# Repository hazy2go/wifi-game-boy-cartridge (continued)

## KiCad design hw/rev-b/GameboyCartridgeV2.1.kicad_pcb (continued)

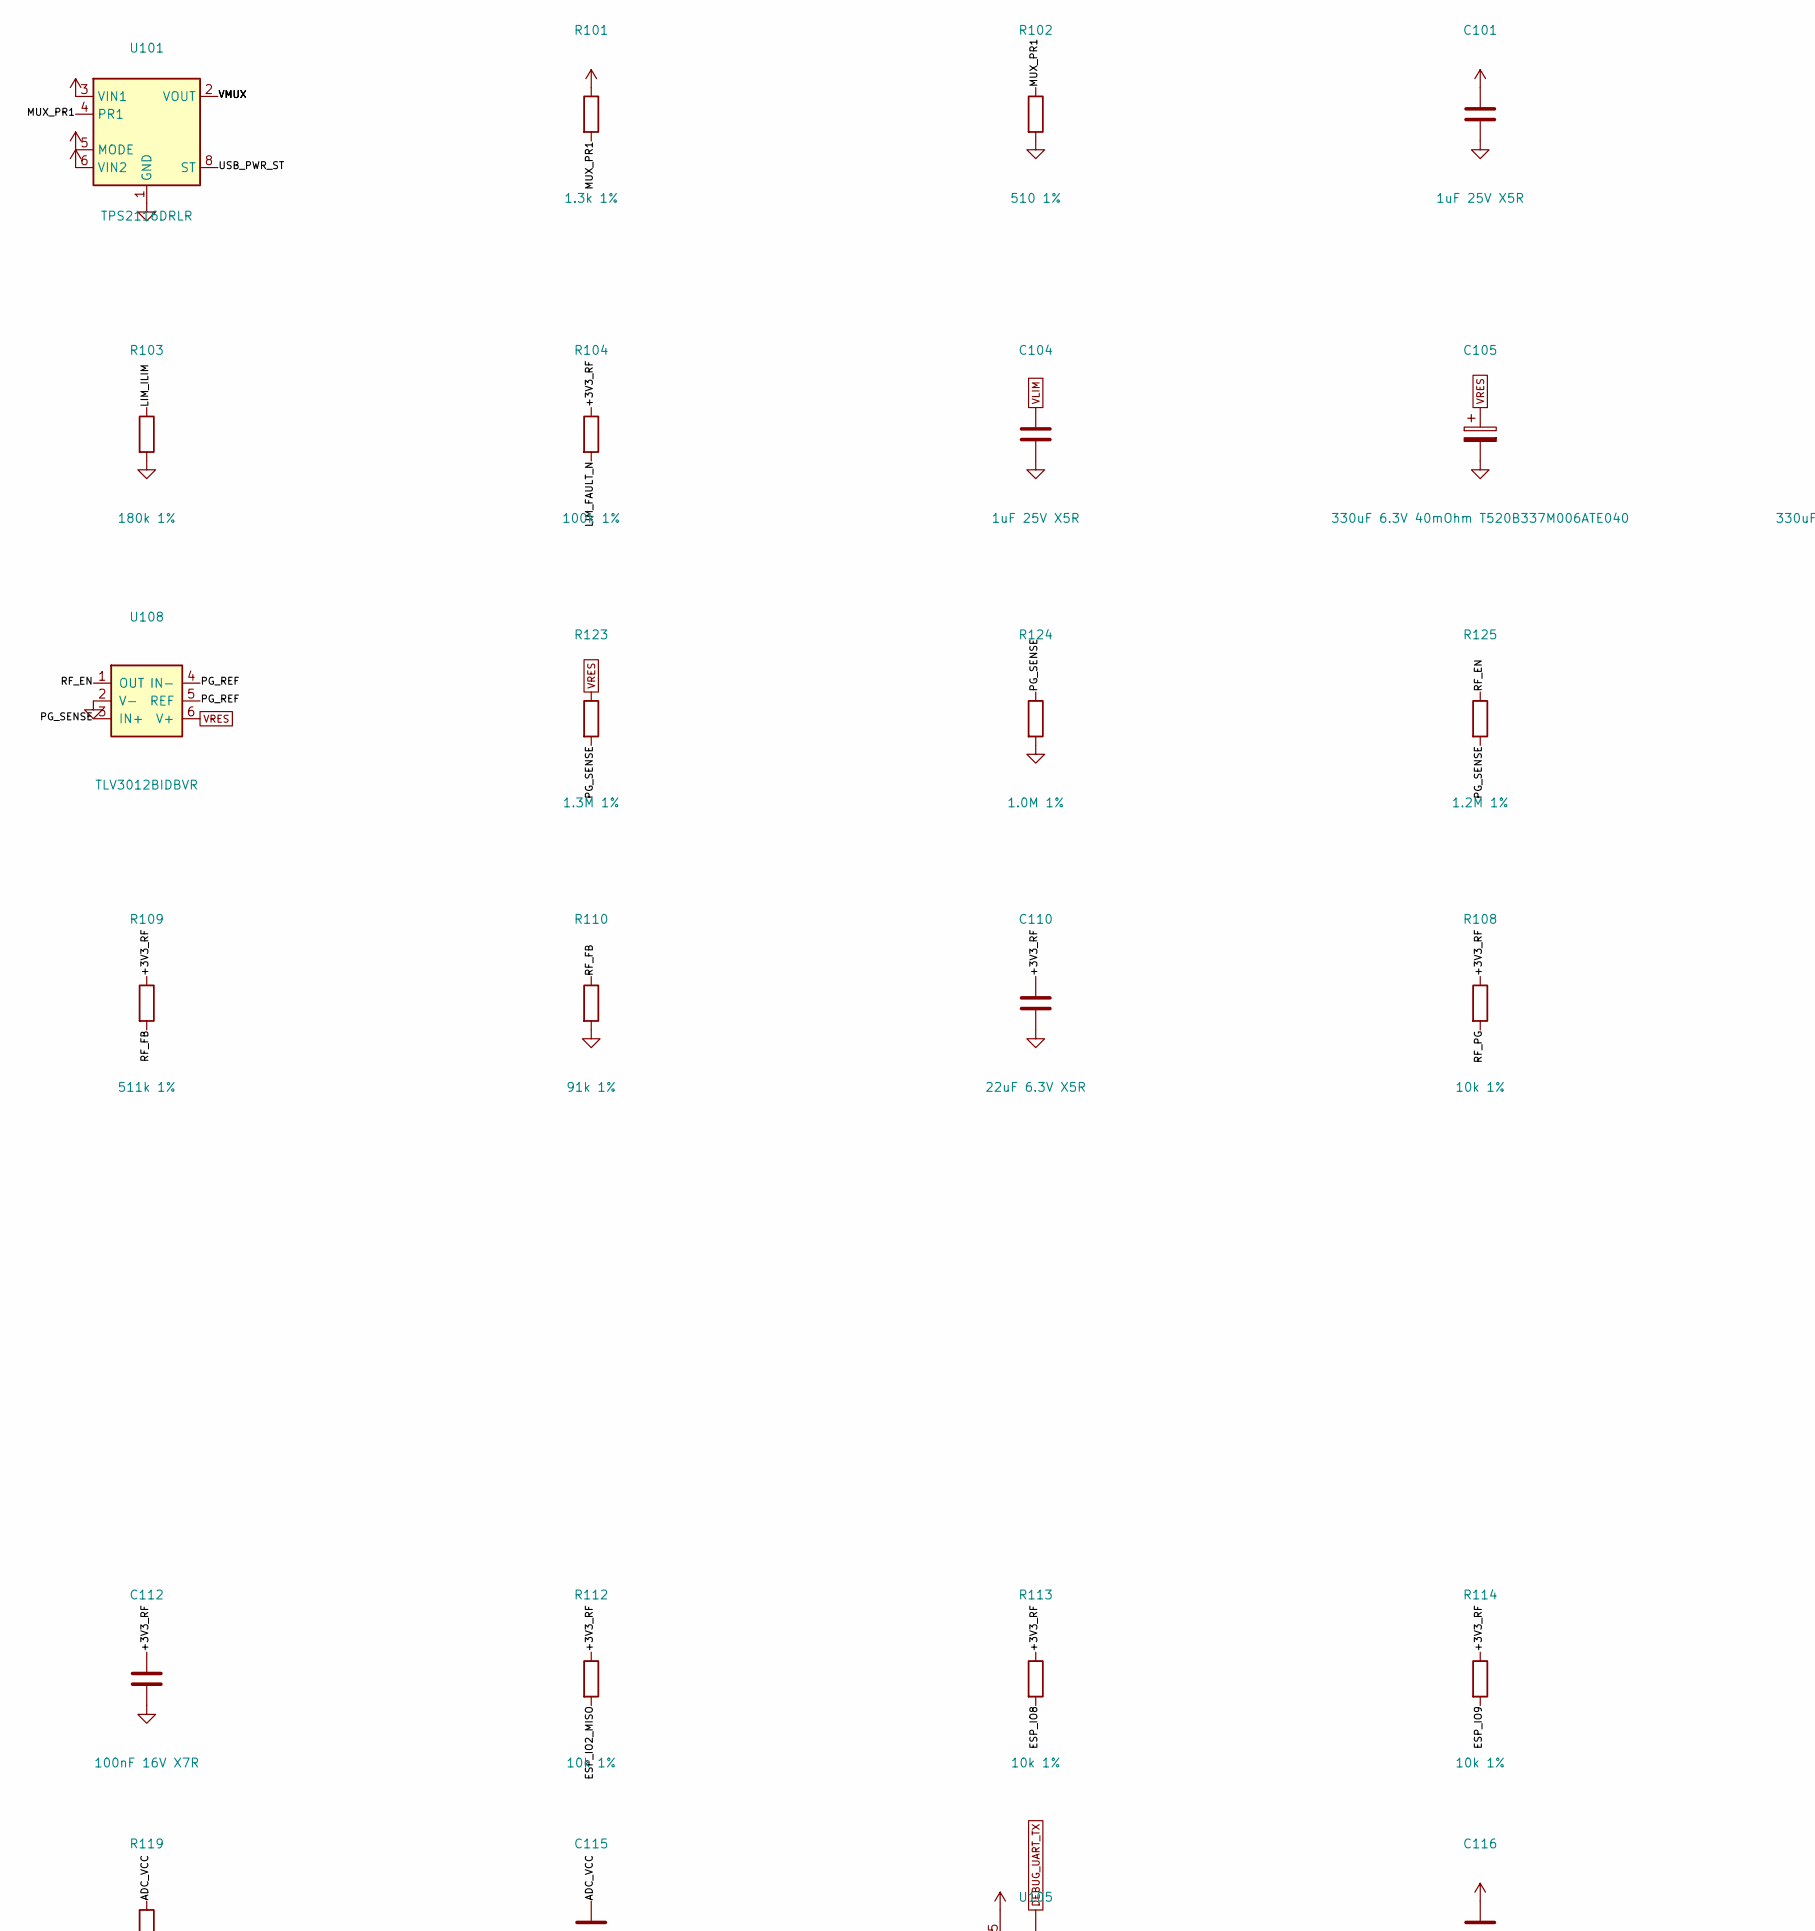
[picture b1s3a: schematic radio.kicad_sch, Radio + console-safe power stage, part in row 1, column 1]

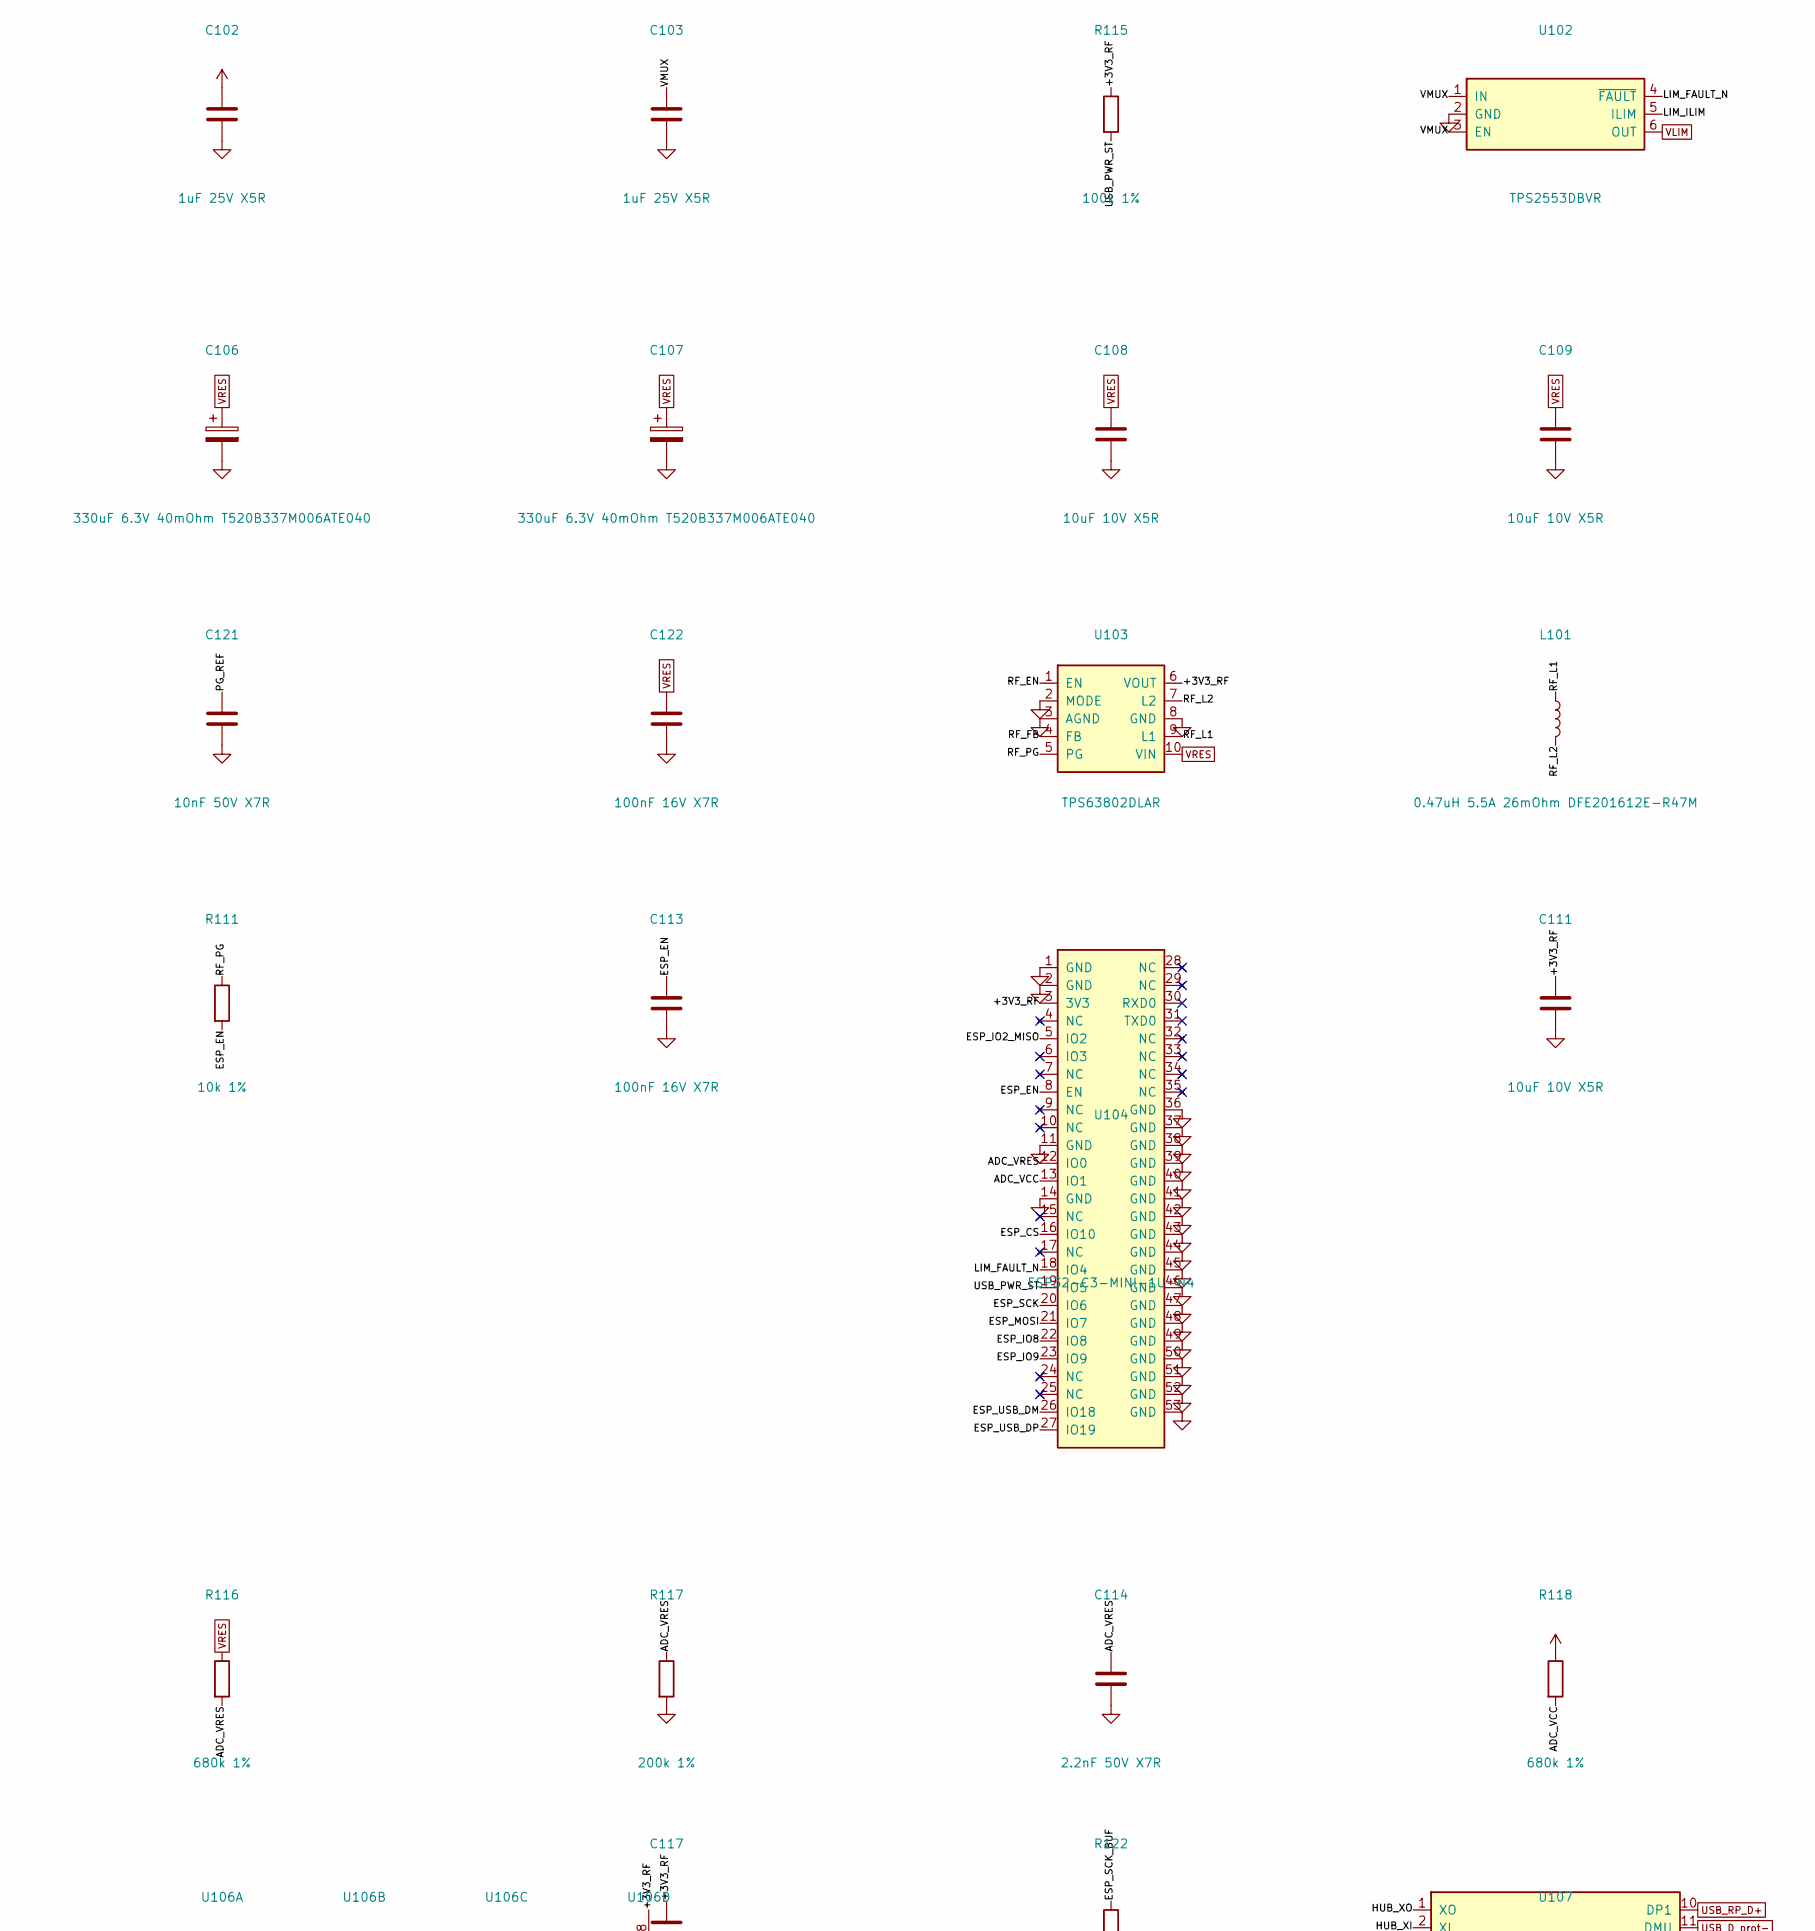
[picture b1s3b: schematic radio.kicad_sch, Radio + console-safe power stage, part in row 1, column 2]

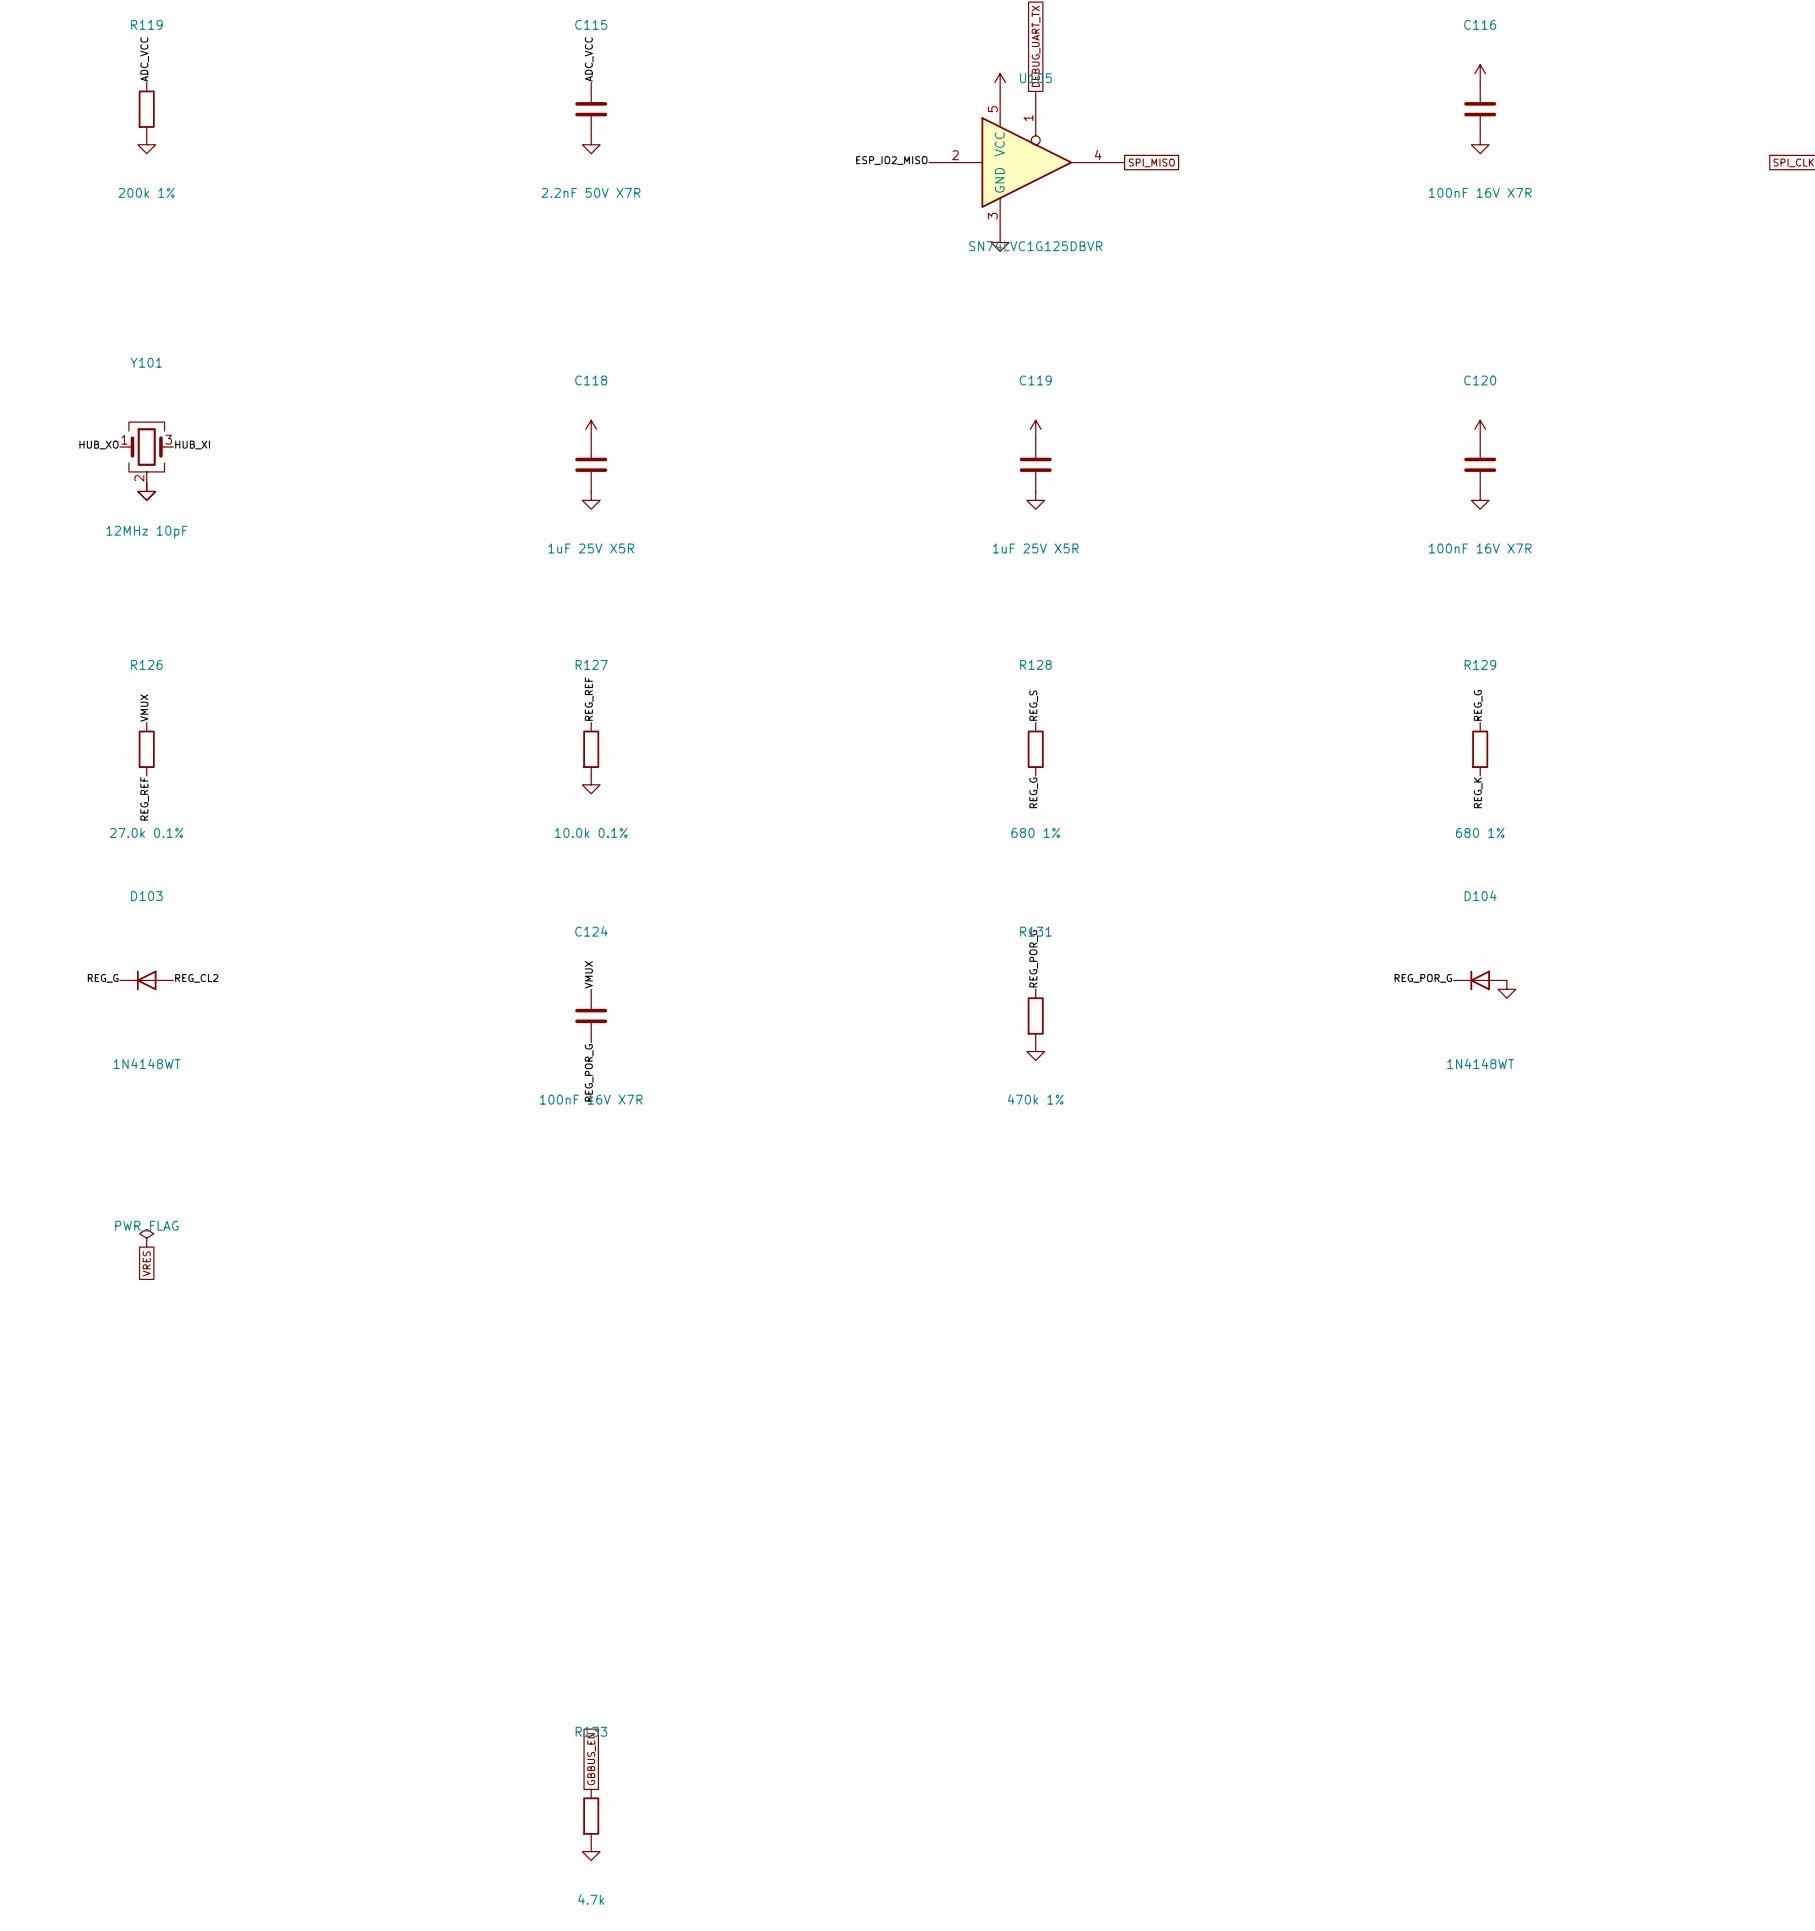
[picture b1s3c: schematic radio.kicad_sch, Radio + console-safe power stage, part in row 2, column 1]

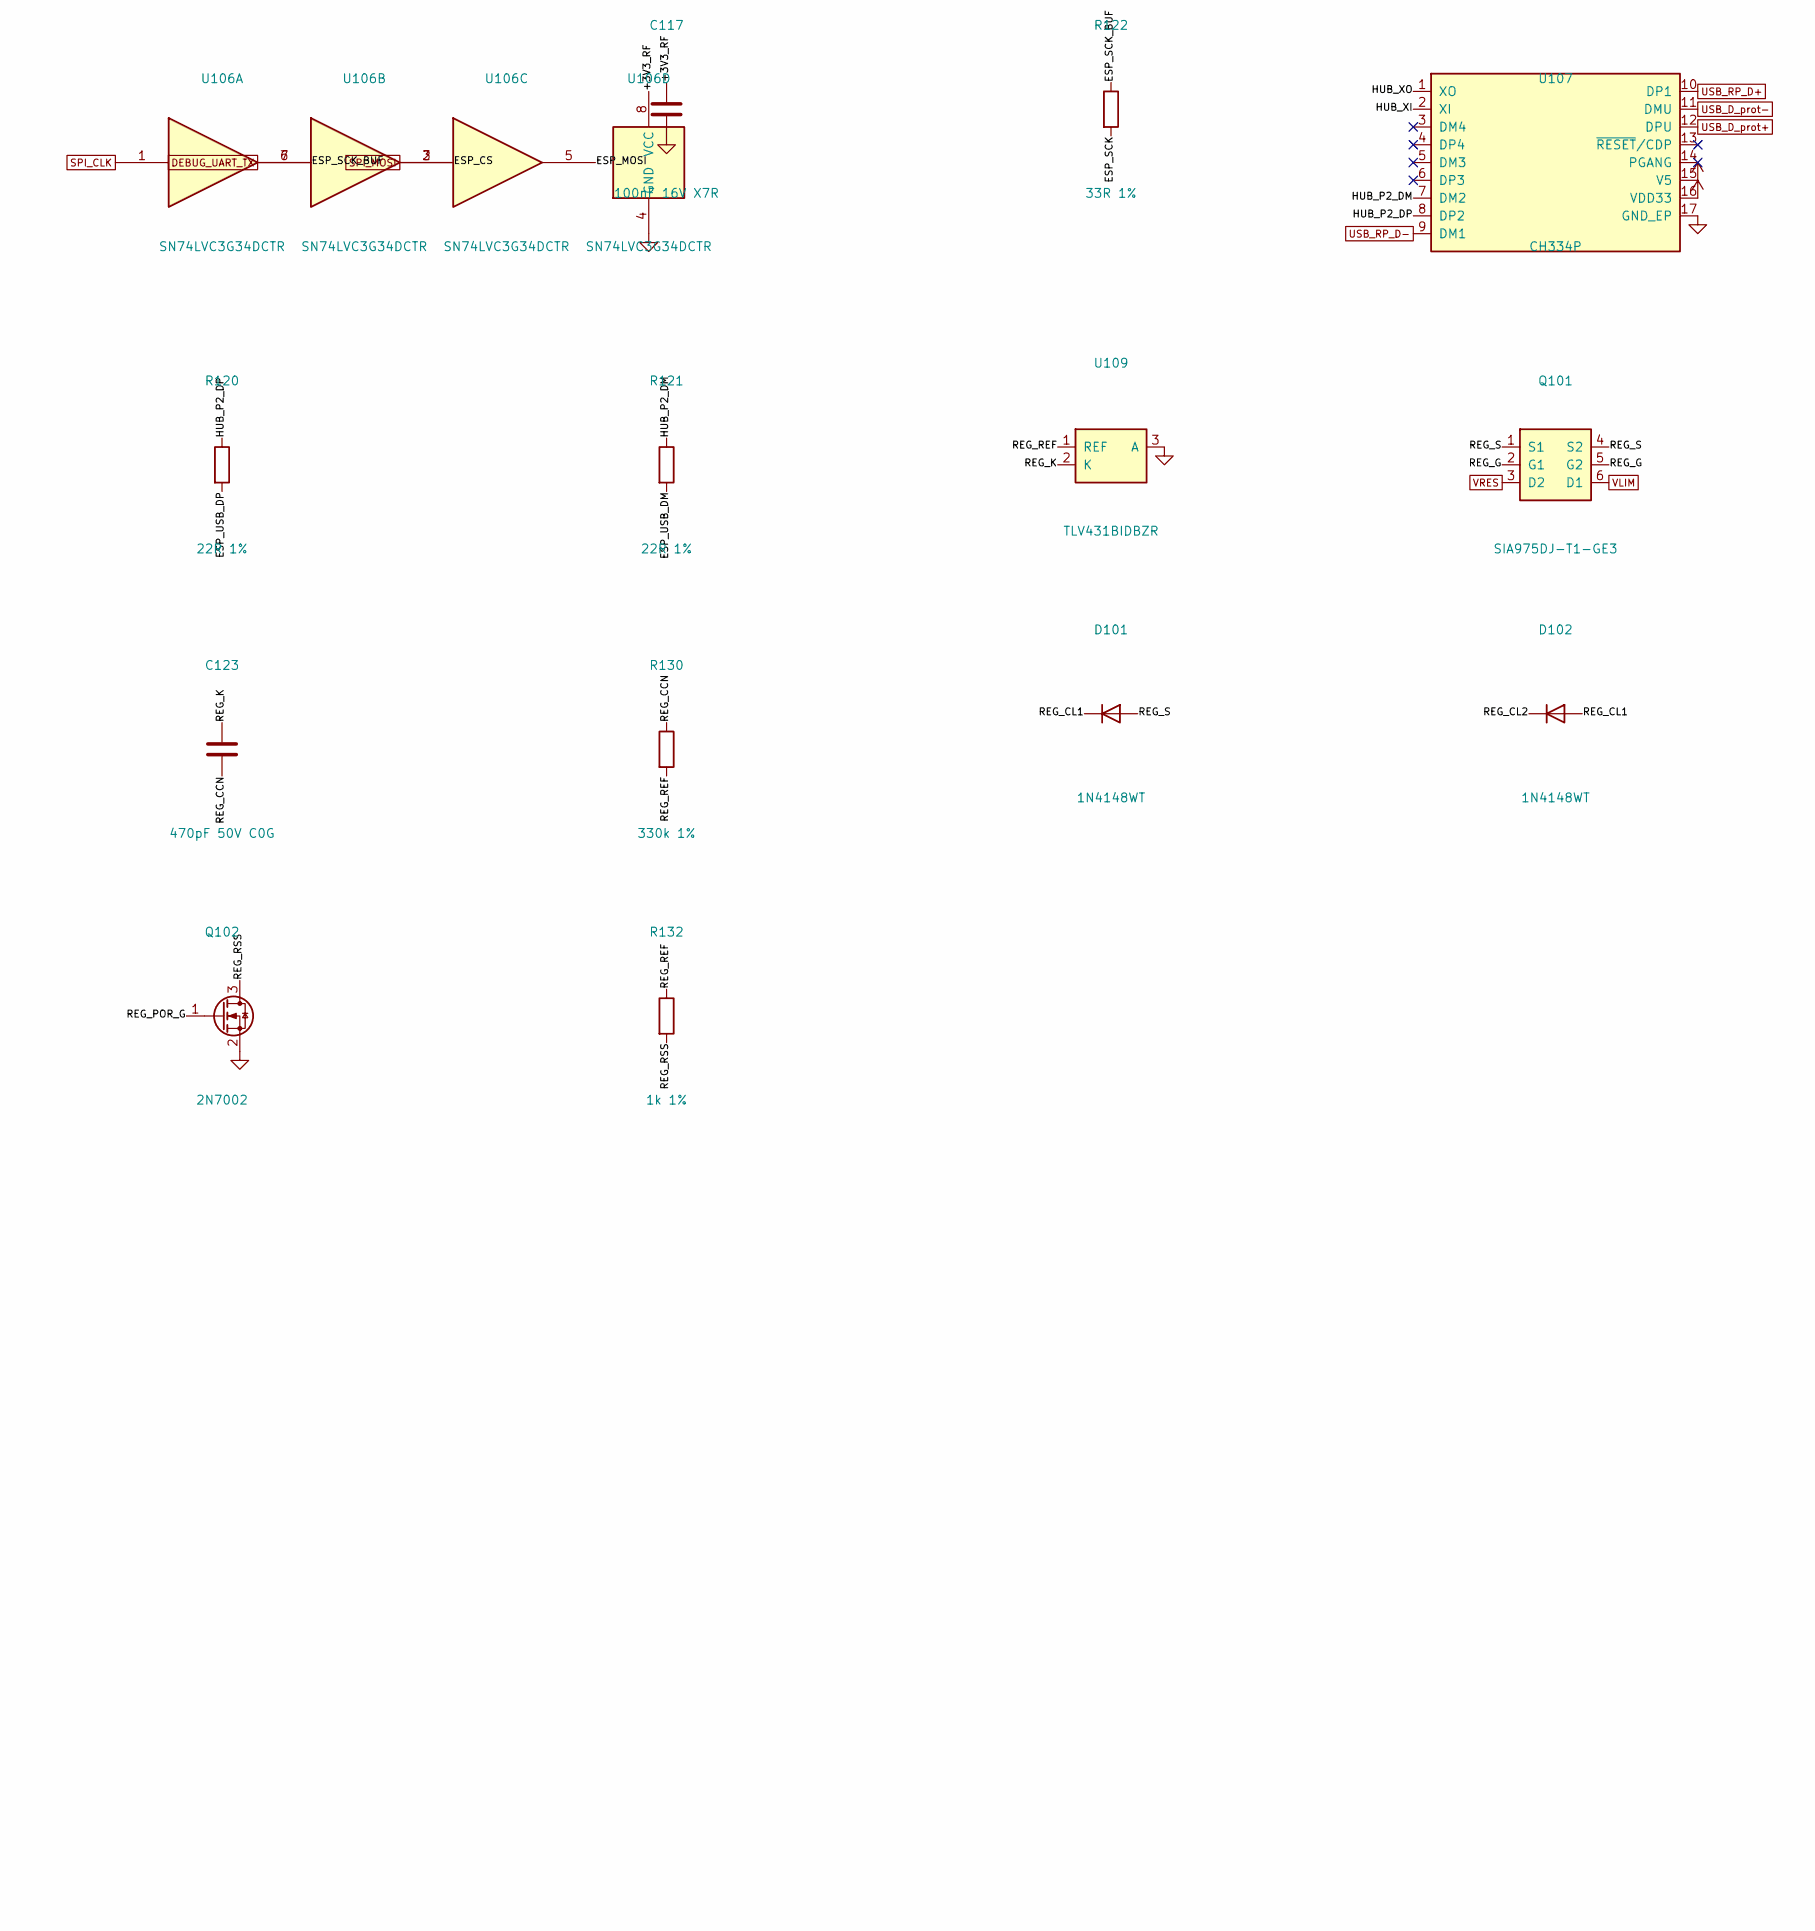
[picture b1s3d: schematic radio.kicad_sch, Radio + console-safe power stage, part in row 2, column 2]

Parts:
C101, C102, C103, C104, C118, C119: 1uF 25V X5R; C_0402_1005Metric; LCSC C52923
C105, C106, C107: 330uF 6.3V 40mOhm T520B337M006ATE040; CP_EIA-3528-21_Kemet-B; LCSC C696806
C108, C109, C111: 10uF 10V X5R; C_0603_1608Metric; LCSC C19702
C110: 22uF 6.3V X5R; C_0603_1608Metric; LCSC C59461
C112, C113, C116, C117, C120, C122, C124: 100nF 16V X7R; C_0402_1005Metric; LCSC C1525
C114, C115: 2.2nF 50V X7R; C_0402_1005Metric; LCSC C84703
C121: 10nF 50V X7R; C_0402_1005Metric; LCSC C15195
C123: 470pF 50V C0G; C_0402_1005Metric; LCSC C76971
D101, D102, D103, D104: 1N4148WT; D_SOD-523; LCSC C27748
L101: 0.47uH 5.5A 26mOhm DFE201612E-R47M; L_Murata_DFE201610P; LCSC C668312
Q101: SIA975DJ-T1-GE3; Vishay_PowerPAK_SC70-6L_Dual; LCSC C141597
Q102: 2N7002; SOT-23; LCSC C8545
R101: 1.3k 1%; R_0402_1005Metric; LCSC C25866
R102: 510 1%; R_0402_1005Metric; LCSC C25123
R103: 180k 1%; R_0402_1005Metric; LCSC C25760
R104, R115: 100k 1%; R_0402_1005Metric; LCSC C25741
R108, R111, R112, R113, R114: 10k 1%; R_0402_1005Metric; LCSC C25744
R109: 511k 1%; R_0402_1005Metric; LCSC C64042
R110: 91k 1%; R_0402_1005Metric; LCSC C453777
R116, R118: 680k 1%; R_0402_1005Metric; LCSC C4131
R117, R119: 200k 1%; R_0402_1005Metric; LCSC C25764
R120, R121: 22R 1%; R_0402_1005Metric; LCSC C25092
R122: 33R 1%; R_0402_1005Metric; LCSC C25105
R123: 1.3M 1%; R_0402_1005Metric; LCSC C423245
R124: 1.0M 1%; R_0402_1005Metric; LCSC C26083
R125: 1.2M 1%; R_0402_1005Metric; LCSC C43675
R126: 27.0k 0.1%; R_0402_1005Metric; LCSC C723421
R127: 10.0k 0.1%; R_0402_1005Metric; LCSC C190095
R128, R129: 680 1%; R_0402_1005Metric; LCSC C137948
R130: 330k 1%; R_0402_1005Metric; LCSC C25778
R131: 470k 1%; R_0402_1005Metric; LCSC C25790
R132: 1k 1%; R_0402_1005Metric; LCSC C11702
R133: 4.7k; R_0402_1005Metric; LCSC C25900
U101: TPS2116DRLR; SOT-583-8; LCSC C3235557
U102: TPS2553DBVR; SOT-23-6; LCSC C55266
U103: TPS63802DLAR; TI_DLA0010A_VSON-HR-10_2x3mm_P0.5mm; LCSC C2845237
U104: ESP32-C3-MINI-1U-N4; ESP32-C3-MINI-1U; LCSC C2911374
U105: SN74LVC1G125DBVR; SOT-23-5; LCSC C23654
U106: SN74LVC3G34DCTR; SSOP-8_2.95x2.8mm_P0.65mm; LCSC C139356
U107: CH334P; QFN-16-1EP_3x3mm_P0.5mm_EP1.75x1.75mm; LCSC C5373042
U108: TLV3012BIDBVR; SOT-23-6; LCSC C20345924
U109: TLV431BIDBZR; SOT-23; LCSC C398375
Y101: 12MHz 10pF; Crystal_SMD_3225-4Pin_3.2x2.5mm; LCSC C20625731

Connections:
+3V3: C116.1, C118.1, C119.1, C120.1, U105.5 (VCC), U107.15 (V5), U107.16 (VDD33); also elsewhere on the board
/Radio/+3V3_RF: C110.1, C111.1, C112.1, C117.1, R104.1, R108.1, R109.1, R112.1, R113.1, R114.1, R115.1, U103.6 (VOUT), U104.3 (3V3), U106.8 (VCC)
/Radio/ADC_VCC: C115.1, R118.2, R119.1, U104.13 (IO1)
/Radio/ADC_VRES: C114.1, R116.2, R117.1, U104.12 (IO0)
/Radio/ESP_CS: U104.16 (IO10), U106.2
/Radio/ESP_EN: C113.1, R111.2, U104.8 (EN)
/Radio/ESP_IO2_MISO: R112.2, U104.5 (IO2), U105.2
/Radio/ESP_IO8: R113.2, U104.22 (IO8)
/Radio/ESP_IO9: R114.2, U104.23 (IO9)
/Radio/ESP_MOSI: U104.21 (IO7), U106.5
/Radio/ESP_SCK: R122.2, U104.20 (IO6)
/Radio/ESP_SCK_BUF: R122.1, U106.7
/Radio/ESP_USB_DM: R121.2, U104.26 (IO18)
/Radio/ESP_USB_DP: R120.2, U104.27 (IO19)
/Radio/HUB_P2_DM: R121.1, U107.7 (DM2)
/Radio/HUB_P2_DP: R120.1, U107.8 (DP2)
/Radio/HUB_XI: U107.2 (XI), Y101.3
/Radio/HUB_XO: U107.1 (XO), Y101.1
/Radio/LIM_FAULT_N: R104.2, U102.4 (~FAULT), U104.18 (IO4)
/Radio/LIM_ILIM: R103.1, U102.5 (ILIM)
/Radio/MUX_PR1: R101.2, R102.1, U101.4 (PR1)
/Radio/PG_REF: C121.1, U108.4 (IN-), U108.5 (REF)
/Radio/PG_SENSE: R123.2, R124.1, R125.2, U108.3 (IN+)
/Radio/REG_CCN: C123.2, R130.1
/Radio/REG_CL1: D101.1 (K), D102.2 (A)
/Radio/REG_CL2: D102.1 (K), D103.2 (A)
/Radio/REG_G: D103.1 (K), Q101.2 (G1), Q101.5 (G2), R128.2, R129.1
/Radio/REG_K: C123.1, R129.2, U109.2 (K)
/Radio/REG_POR_G: C124.2, D104.1 (K), Q102.1 (G), R131.1
/Radio/REG_REF: R126.2, R127.1, R130.2, R132.1, U109.1 (REF)
/Radio/REG_RSS: Q102.3 (D), R132.2
/Radio/REG_S: D101.2 (A), Q101.1 (S1), Q101.4 (S2), R128.1
/Radio/RF_EN: R125.1, U103.1 (EN), U108.1 (OUT)
/Radio/RF_FB: R109.2, R110.1, U103.4 (FB)
/Radio/RF_L1: L101.1, U103.9 (L1)
/Radio/RF_L2: L101.2, U103.7 (L2)
/Radio/RF_PG: R108.2, R111.1, U103.5 (PG)
/Radio/USB_PWR_ST: R115.2, U101.8 (ST), U104.19 (IO5)
/Radio/VMUX: C103.1, C124.1, R126.1, U101.2 (VOUT), U101.7 (VOUT), U102.1 (IN), U102.3 (EN)
DEBUG_UART_TX: U105.1, U106.6; also elsewhere on the board
GBBUS_EN: R133.1; also elsewhere on the board
GND: C101.2, C102.2, C103.2, C104.2, C105.2, C106.2, C107.2, C108.2, C109.2, C110.2, C111.2, C112.2, C113.2, C114.2, C115.2, C116.2, C117.2, C118.2, C119.2, C120.2, C121.2, C122.2, D104.2 (A), Q102.2 (S), R102.2, R103.2, R110.2, R117.2, R119.2, R124.2, R127.2, R131.2, R133.2, U101.1 (GND), U102.2 (GND), U103.2 (MODE), U103.3 (AGND), U103.8 (GND), U104.1 (GND), U104.2 (GND), U104.11 (GND), U104.14 (GND), U104.36 (GND), U104.37 (GND), U104.38 (GND), U104.39 (GND), U104.40 (GND), U104.41 (GND), U104.42 (GND), U104.43 (GND), U104.44 (GND), U104.45 (GND), U104.46 (GND), U104.47 (GND), U104.48 (GND), U104.49 (GND), U104.50 (GND), U104.51 (GND), U104.52 (GND), U104.53 (GND), U105.3 (GND), U106.4 (GND), U107.17 (GND_EP), U108.2 (V-), U109.3 (A), Y101.2 (G), Y101.4 (G); also elsewhere on the board
SPI_CLK: U106.1; also elsewhere on the board
SPI_MISO: U105.4; also elsewhere on the board
SPI_MOSI: U106.3; also elsewhere on the board
USB_D_prot+: U107.12 (DPU); also elsewhere on the board
USB_D_prot-: U107.11 (DMU); also elsewhere on the board
USB_RP_D+: U107.10 (DP1); also elsewhere on the board
USB_RP_D-: U107.9 (DM1); also elsewhere on the board
VBUS: C101.1, R101.1, U101.3 (VIN1), U101.5 (MODE); also elsewhere on the board
VCC: C102.1, R118.1, U101.6 (VIN2); also elsewhere on the board
VLIM: C104.1, Q101.6 (D1), U102.6 (OUT)
VRES: C105.1, C106.1, C107.1, C108.1, C109.1, C122.1, Q101.3 (D2), R116.1, R123.1, U103.10 (VIN), U108.6 (V+)

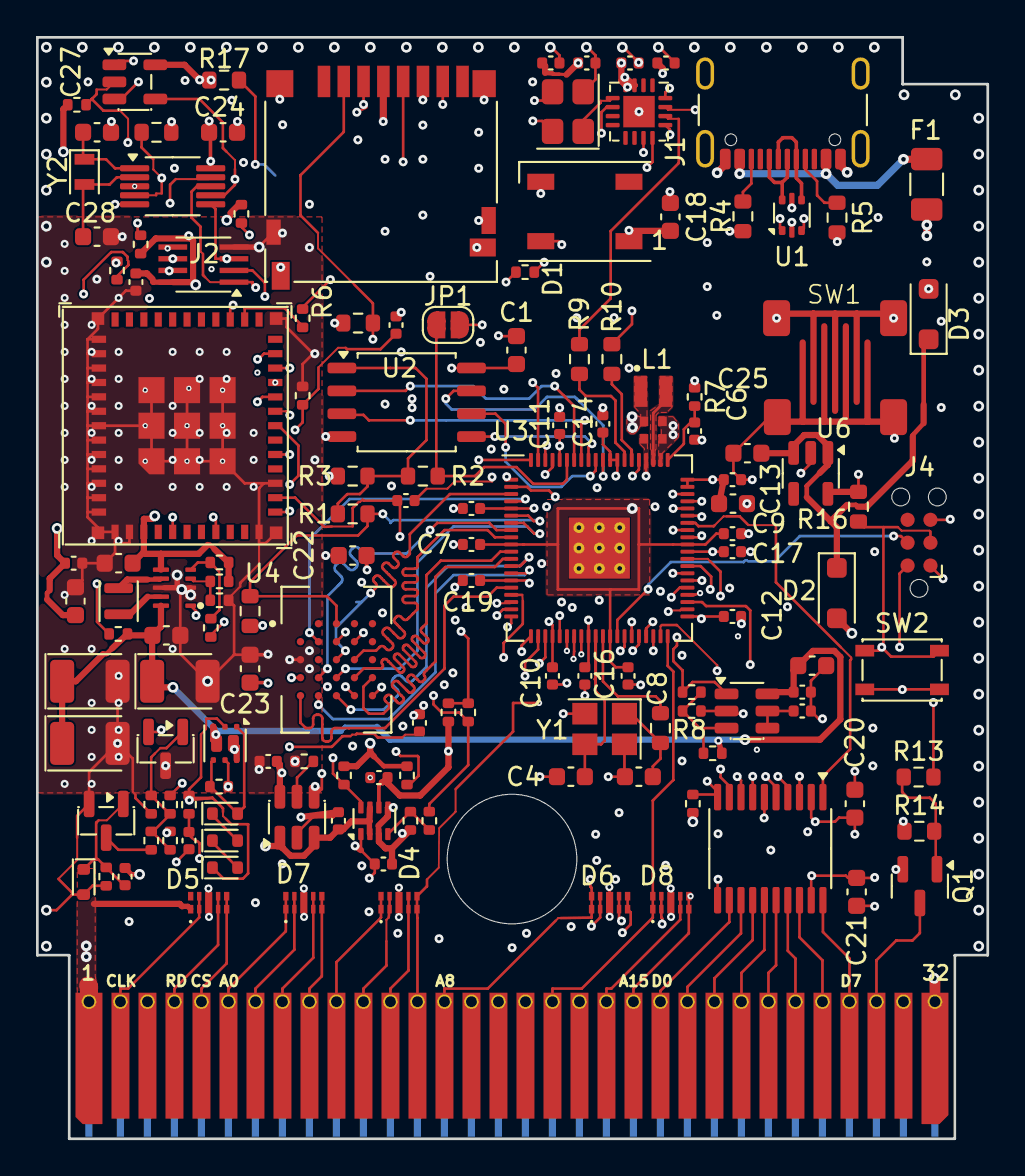
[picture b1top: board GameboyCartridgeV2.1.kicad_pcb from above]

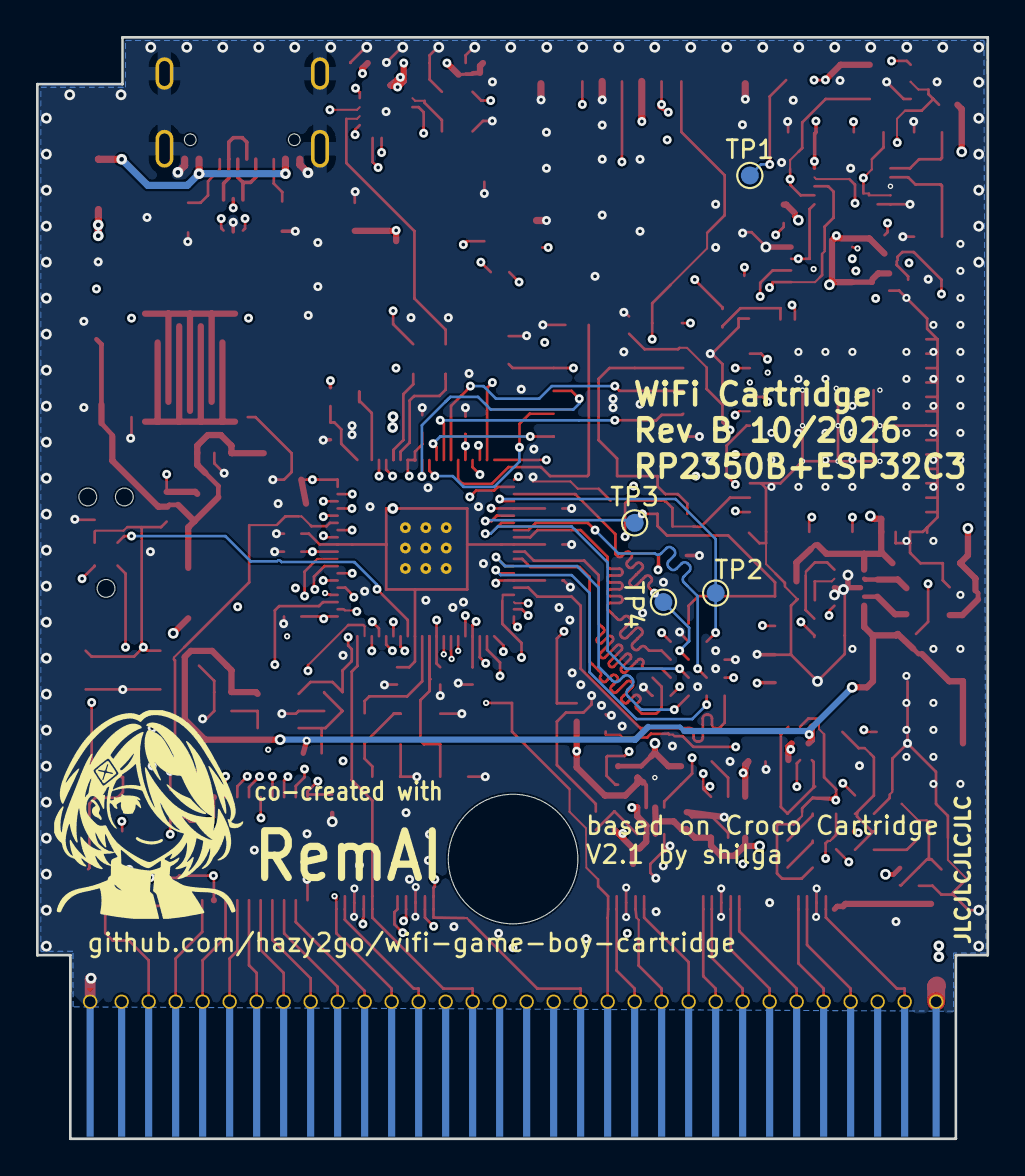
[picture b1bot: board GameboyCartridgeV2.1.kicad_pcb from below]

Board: 6 copper layers, 52.8 x 61.2 mm, 146 parts (4 on the bottom side), 133 nets.

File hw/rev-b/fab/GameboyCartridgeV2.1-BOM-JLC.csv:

Comment,Designator,Footprint,LCSC Part #
100nF,"C1,C18,C20,C21,C22,C23,C24",C_0603_1608Metric,C14663
4.7u,"C2,C3",C_0402_1005Metric_small_pads,C23733
15pF,"C4,C5",C_0603_1608Metric,C1644
4.7u,"C6,C8",C_0402_1005Metric,C23733
100n,"C7,C9,C10,C11,C12,C13,C14,C15,C16,C17,C19",C_0402_1005Metric,C1525
1uF,"C25,C26",C_0603_1608Metric,C15849
4.3pF,"C27,C28",C_0603_1608Metric,C59526
1uF 25V X5R,"C101,C102,C103,C104,C118,C119",C_0402_1005Metric,C52923
330uF 6.3V 40mOhm T520B337M006ATE040,"C105,C106,C107",CP_EIA-3528-21_Kemet-B,C696806
10uF 10V X5R,"C108,C109,C111",C_0603_1608Metric,C19702
22uF 6.3V X5R,C110,C_0603_1608Metric,C59461
100nF 16V X7R,"C112,C113,C116,C117,C120,C122,C124",C_0402_1005Metric,C1525
2.2nF 50V X7R,"C114,C115",C_0402_1005Metric,C84703
10nF 50V X7R,C121,C_0402_1005Metric,C15195
470pF 50V C0G,C123,C_0402_1005Metric,C76971
WS2812B,D1,LED_WS2812B_PLCC4_5.0x5.0mm_P3.2mm,C2761795
D_Schottky,"D2,D3",D_SOD-123F,C669022
1N4148WT,"D101,D102,D103,D104",D_SOD-523,C27748
Polyfuse,F1,Fuse_1206_3216Metric,C2649911
USB_C_Receptacle_USB2.0,J1,USB_C_Receptacle_GCT_USB4105-xx-A_16P_TopMnt_Horizontal,C2927037
Micro_SD_Card_Det2,J2,microSD_HC_Hirose_DM3D-SF,C719027
3.3u,L1,L_pol_2016,C42411119
0.47uH 5.5A 26mOhm DFE201612E-R47M,L101,L_Murata_DFE201610P,C668312
CJ2302,Q1,SOT-23,C8548
SIA975DJ-T1-GE3,Q101,Vishay_PowerPAK_SC70-6L_Dual,C141597
2N7002,Q102,SOT-23,C8545
0R,R2,R_0603_1608Metric,C21189
10k,"R3,R6,R12,R14,R15,R16",R_0603_1608Metric,C25804
5k1,"R4,R5",R_0603_1608Metric,C23186
33,R7,R_0402_1005Metric,C25105
1k,"R8,R13",R_0603_1608Metric,C21190
27R,"R9,R10",R_0603_1608Metric,C25190
1.3k 1%,R101,R_0402_1005Metric,C25866
510 1%,R102,R_0402_1005Metric,C25123
180k 1%,R103,R_0402_1005Metric,C25760
100k 1%,"R104,R115",R_0402_1005Metric,C25741
10k 1%,"R108,R111,R112,R113,R114",R_0402_1005Metric,C25744
511k 1%,R109,R_0402_1005Metric,C64042
91k 1%,R110,R_0402_1005Metric,C453777
680k 1%,"R116,R118",R_0402_1005Metric,C4131
200k 1%,"R117,R119",R_0402_1005Metric,C25764
22R 1%,"R120,R121",R_0402_1005Metric,C25092
33R 1%,R122,R_0402_1005Metric,C25105
1.3M 1%,R123,R_0402_1005Metric,C423245
1.0M 1%,R124,R_0402_1005Metric,C26083
1.2M 1%,R125,R_0402_1005Metric,C43675
27.0k 0.1%,R126,R_0402_1005Metric,C723421
10.0k 0.1%,R127,R_0402_1005Metric,C190095
680 1%,"R128,R129",R_0402_1005Metric,C137948
330k 1%,R130,R_0402_1005Metric,C25778
470k 1%,R131,R_0402_1005Metric,C25790
1k 1%,R132,R_0402_1005Metric,C11702
4.7k,R133,R_0402_1005Metric,C25900
USBLC6-2P6,U1,SOT-666,C2827693
W25Q128JVSIQ,U2,SOIC-8_5.23x5.23mm_P1.27mm,C97521
RP2350_80QFN,U3,RP2350-QFN-80-1EP_10x10_P0.4mm_EP3.4x3.4mm_ThermalVias,C42415655
IS66WVH8M8BLL-100B1LI,U4,BGA25C100P5X5_800X600X120N,C1349096
MCP79510,U5,MSOP-10_3x3mm_P0.5mm,C627708
AP2112K-3.3,U6,SOT-23-5,C51118
TXB0108PW,U7,TSSOP-20_4.4x6.5mm_P0.65mm,C53406
TPS2116DRLR,U101,SOT-583-8,C3235557
TPS2553DBVR,U102,SOT-23-6,C55266
TPS63802DLAR,U103,TI_DLA0010A_VSON-HR-10_2x3mm_P0.5mm,C2845237
ESP32-C3-MINI-1U-N4,U104,ESP32-C3-MINI-1U,C2911374
SN74LVC1G125DBVR,U105,SOT-23-5,C23654
SN74LVC3G34DCTR,U106,SSOP-8_2.95x2.8mm_P0.65mm,C139356
CH334P,U107,QFN-16-1EP_3x3mm_P0.5mm_EP1.75x1.75mm,C5373042
TLV3012BIDBVR,U108,SOT-23-6,C20345924
TLV431BIDBZR,U109,SOT-23,C398375
12MHz,Y1,Crystal_SMD_TXC_7M-4Pin_3.2x2.5mm,C20625731
32.768kHz,Y2,Crystal_SMD_TXC_9HT11-2Pin_2.0x1.2mm,C97602
12MHz 10pF,Y101,Crystal_SMD_3225-4Pin_3.2x2.5mm,C20625731

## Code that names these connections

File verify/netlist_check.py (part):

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  MULTI_DRIVER     two different parts with output/power_out pins on one net
  REF_DUP          duplicated reference, or a reference that clashes with a Croco reference
  BOM              missing/invalid LCSC number or footprint; footprint not found in KiCad libs
  STRAP            ESP32-C3 strapping pin GPIO2/GPIO8/GPIO9 without a defined boot level
                   (required: GPIO2=1, GPIO8=1, GPIO9=1 -> SPI boot, ESP32-C3-MINI-1 DS Table 4-3)
  CROCO_EDIT       a croco_edits entry that does not match the Croco netlist

Usage:
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
KNOWN_SOURCES = {'GND', 'VCC', 'VBUS', '+3V3'}      # supplied by Croco / the cartridge slot / USB
DRIVER_TYPES = {'output', 'power_out'}
STRAPS = {'IO2': '1', 'IO8': '1', 'IO9': '1'}       # ESP32-C3 SPI boot (Table 4-3), GPIO8=1 for download
ESP_SYMBOL = 'radio:ESP32-C3-MINI-1U'

# ------------------------------------------------------------------ s-expressions / KiCad libs
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        part(d, 'C117')['pins']['1'] = 'SELFTEST_UNPOWERED'

    def m_two_drivers(d):
        part(d, 'U108')['pins']['1'] = 'VMUX'

    def m_dup_ref(d):
        part(d, 'R102')['ref'] = 'R101'
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
    def m_strap_missing(d):
        d['parts'].remove(part(d, 'R112'))
        part(d, 'U104')['pins']['5'] = 'ESP_IO2_MISO'

    def m_power_nc(d):
        part(d, 'U107')['pins']['15'] = 'NC'
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             ('single-pin net', m_single_net, 'SINGLE_NET'), ('unpowered rail', m_no_source, 'NO_SOURCE'),
             ('comparator output onto VMUX', m_two_drivers, 'MULTI_DRIVER'), ('duplicate ref', m_dup_ref, 'REF_DUP'),
             ('Croco ref clash', m_croco_ref, 'REF_DUP'), ('missing LCSC', m_no_lcsc, 'BOM'),
             ('missing footprint', m_bad_fp, 'BOM'), ('GPIO9 strapped low', m_strap_low, 'STRAP'),
             ('GPIO2 pull-up removed', m_strap_missing, 'STRAP'), ('hub V5 NC', m_power_nc, 'POWER_NC'),
             ('unknown symbol', m_bad_symbol, 'SYMBOL'), ('bad Croco edit', m_bad_edit, 'CROCO_EDIT')]
    ok = True
    for label, fn, want in cases:
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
